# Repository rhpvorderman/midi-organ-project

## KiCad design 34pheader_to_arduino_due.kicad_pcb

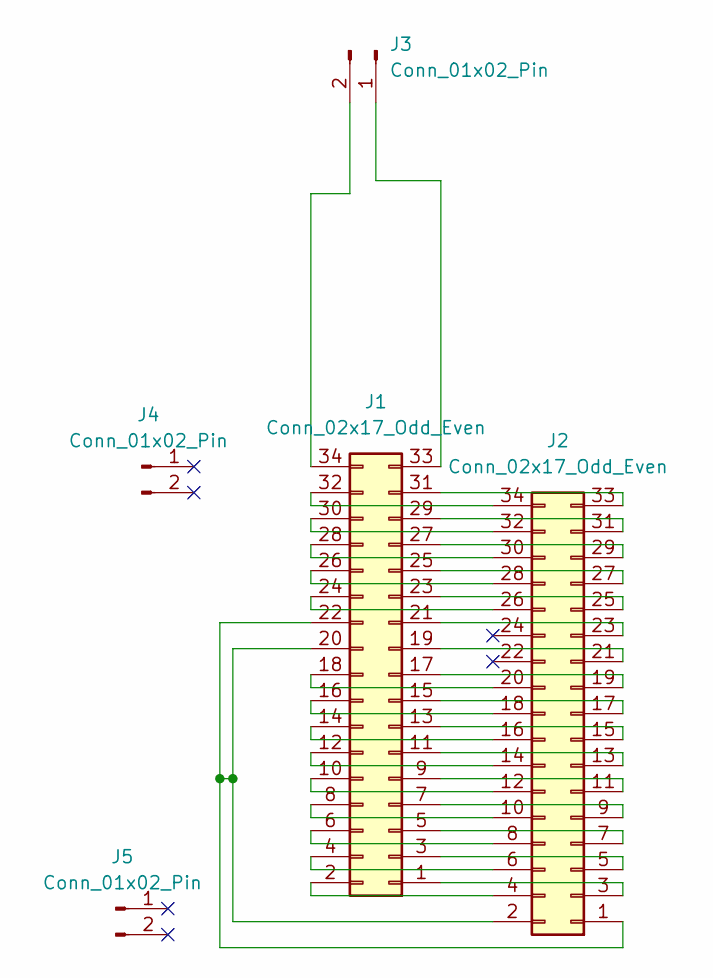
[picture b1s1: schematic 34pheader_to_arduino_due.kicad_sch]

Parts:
J1, J2: Conn_02x17_Odd_Even
J3, J4, J5: Conn_01x02_Pin

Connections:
unnamed: J1.1, J2.3
unnamed: J1.2, J2.4
unnamed: J1.3, J2.5
unnamed: J1.4, J2.6
unnamed: J1.5, J2.7
unnamed: J1.6, J2.8
unnamed: J1.7, J2.9
unnamed: J1.8, J2.10
unnamed: J1.9, J2.11
unnamed: J1.10, J2.12
unnamed: J1.11, J2.13
unnamed: J1.12, J2.14
unnamed: J1.13, J2.15
unnamed: J1.14, J2.16
unnamed: J1.15, J2.17
unnamed: J1.16, J2.18
unnamed: J1.17, J2.19
unnamed: J1.18, J2.20
unnamed: J1.19, J2.21
unnamed: J1.20, J1.22, J2.1, J2.2
unnamed: J1.21, J2.23
unnamed: J1.23, J2.25
unnamed: J1.24, J2.26
unnamed: J1.25, J2.27
unnamed: J1.26, J2.28
unnamed: J1.27, J2.29
unnamed: J1.28, J2.30
unnamed: J1.29, J2.31
unnamed: J1.30, J2.32
unnamed: J1.31, J2.33
unnamed: J1.32, J2.34
unnamed: J1.33, J3.1
unnamed: J1.34, J3.2

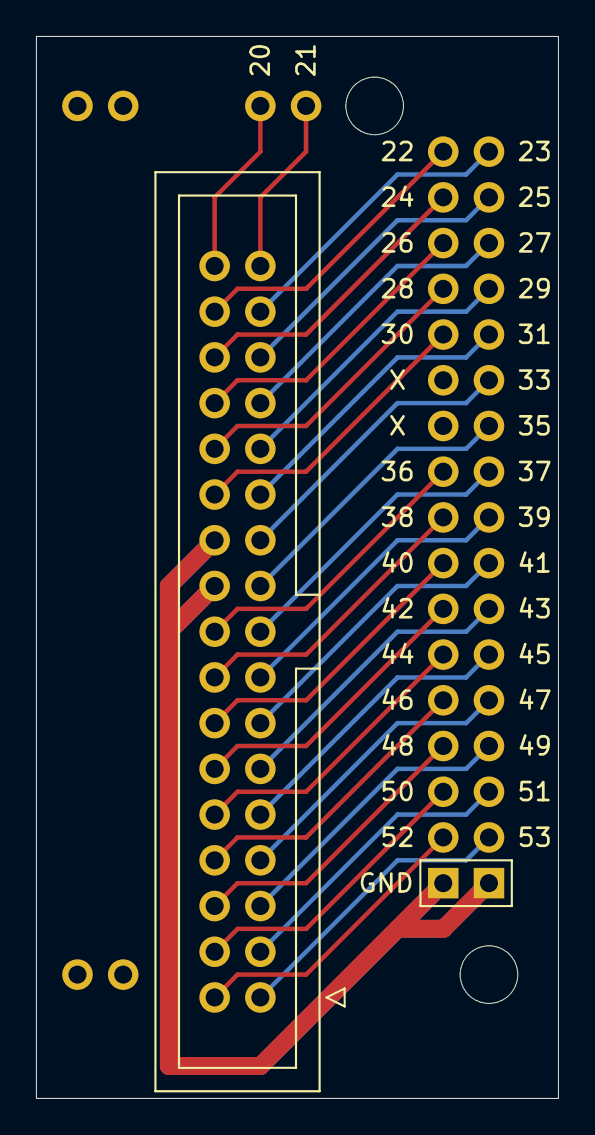
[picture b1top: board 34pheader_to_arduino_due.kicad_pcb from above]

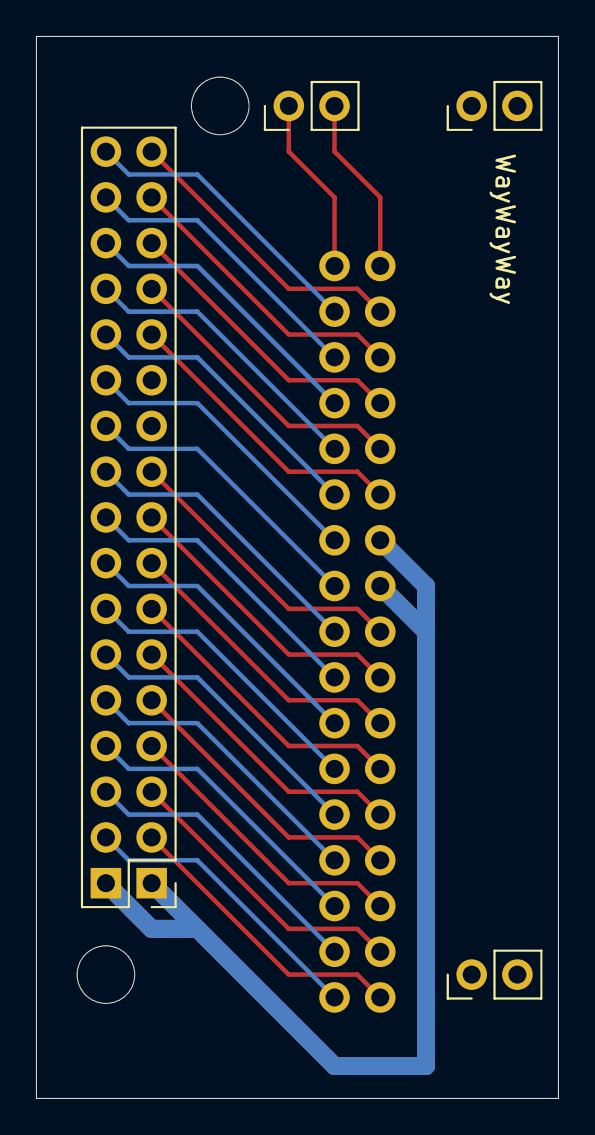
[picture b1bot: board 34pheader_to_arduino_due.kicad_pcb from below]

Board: 2 copper layers, 29.0 x 59.0 mm, 7 parts (4 on the bottom side), 33 nets.

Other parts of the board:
MountingHole1, MountingHole2: MountingHole_3.2mm_M3

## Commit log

2023-12-07 Add sketch for testing switches
2023-12-11 Start on a kicad design
2023-12-11 Remove text labels, different header placement
2023-12-11 Move pin headers to back of the board
2023-12-11 Set actual track width
2023-12-11 Add schema
2023-12-11 Continue on board design
2023-12-12 Draw an edge cut
2023-12-12 Move IPC header away from the mounting hole
2023-12-12 Correct a track that was not exactly in the middle
2023-12-12 Add WayWayWay text to indicate the project number should be on the back silkscreen
2023-12-12 Add pin numbers on silk screen layer
2023-12-12 Add GND label
2023-12-12 Remove project settings file from project
2023-12-13 Ensure pinout is correct
2023-12-15 Start platformIO project. Map pins to pitches.
2023-12-16 Add function to send midi event
2023-12-16 Add state update routine
2023-12-16 Set tabsize to 4
2023-12-16 Set pins to input pullup and make sure code runs on interrupt
2023-12-16 Add code for waiting to interrupt
2023-12-16 Add explanation for code
2023-12-16 Add an extra comment
2023-12-16 Input PULLUP makes pins LOW
2023-12-18 Led builtin reacts to keypresses
2023-12-18 Simplify code somewhat
2023-12-18 Simplify using a polling model
2023-12-18 Simplify further
2023-12-18 Remove while(true) inside of loop
2023-12-21 Try using serial
2023-12-28 Change to due programming port
2023-12-28 Debug on first key
2023-12-28 Log midi events
2023-12-28 Correct midi event numbers
2023-12-28 Turn note off without velocity
2023-12-28 Remove debug statements
2023-12-29 Make pedal range one octave higher
